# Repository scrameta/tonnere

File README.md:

# Project Tonnere

The EclaireXL was a partially open Atari XL FPGA implementation designed almost
a decade ago. This project is intended to be a fully open community follow-up
version. (It is being renamed **MegaXE**; *tonnere* — deliberately misspelt, to
match "EclaireXL" — is French for thunder, following on from the EclaireXL's
lightning.)

## The Atari core

The FPGA Atari core itself is **not** duplicated here. It lives in the shared
[**atari_xl_fpga_common**](https://github.com/scrameta/atari_xl_fpga_common)
repository — the same core used by the multi-board
[atari_xl_fpga](https://github.com/scrameta/atari_xl_fpga) project — and is
included in this repo as a git submodule at `atari_800xl/common`. This board
project provides the hardware design plus the board-specific top level, clocking,
pin mapping and I/O wrapped around that common core.

## Getting the code

The shared core is a submodule, so clone recursively:

```sh
git clone --recursive https://github.com/scrameta/tonnere

# …or, if you already cloned without --recursive:
git submodule update --init --recursive
```

The core then appears under `atari_800xl/common`. To move onto a newer core
revision, bump the submodule pointer:

```sh
cd atari_800xl/common
git checkout <desired-commit-or-branch>
cd -
git add atari_800xl/common
git commit -m "Bump common core to <rev>"
```

See the
[common repo](https://github.com/scrameta/atari_xl_fpga_common#using-this-repository)
for more on the submodule workflow.

## Status

For now there is only a hardware design, from which a physical board has been
produced. The design goals of this are described below.

## Memory

3 independent banks of RAM from FPGA

- 512KB 16-bit wide 10ns SRAM (for VBXE)
- 2048KB 16-bit wide 10ns SRAM (primary Atari core)
- 32MB 16-bit wide SDRAM (secondary Atari core etc - for large memory expansions, cartridge emulation etc)

## Video output

- HDMI driven directly by FPGA
- Analog video driven by FPGA (3 pins/channel - ~8-bit/channel resolution) filtered/buffered by THS7316.
- NTSC in 480i or 480p, PAL in 576i or 576p
- Polyphasic and area-based scaler allowing 720p, 1080i etc

## Audio output

- PCM5102A DAC

## Audio input

- 12-bit ADC for PBI, SIO, 3.5mm left/right on STM microcontroller

## Joystick ports 1-4

- Directly connected to FPGA (via level shifters)
- Paddle support using STM ADC inputs

## Six USB ports

- 1 USB A internal for keyboard
- 3 USB A external for joystick, keyboard etc
- 1 USB C for power only (next to power switch)
- 1 rear USB C for STM32 DFU (to program it), or to be a mass-storage slave to a PC to copy data on.

## Atari peripheral emulator (ESP32 microcontroller/almost Fujinet)

- Wifi support
- Serial connection to STM32
- SPI master to FPGA (for DMA to RAM, faster than serial via STM)
- SIO pins (all)
- Audio out DAC goes to SIO audio in
- Slave to STM32
- Slave to Atari via SIO
- JTAG for debugging

## Firmware/control (STM32)

- SPI master to FPGA SPI flash chip (to program)
- Can restart FPGA
- SRAM port connected to FPGA (for DMA to Atari core RAM + RAM banks)
- IRQ from FPGA
- 4-bit external SD card interface
- SPI to internal micro SD card (will appear as IDE hard drive to Atari core)
- ADC for sampling (see audio in)
- Serial connection for communication for Atari peripheral emulator
- USB port + stack
- DFU mode for programming, can then program FPGA flash and ESP32 via serial (+BOOT etc).
- HDMI i2c link (to get mode support)
- PLL i2c link (6 programmable clocks for FPGA)
- SWD port for debugging
- UART port for debugging/expansion
- Will run menus etc, via DMA to Atari core (+ potentially framebuffer)

## Atari core (Cyclone 10 LP FPGA)

- Core Atari XL and Atari 800 support
- 2x/4x colour clock Antic/GTIA support
- VBXE
- PokeyMAX
- HDD via IDE emulation on microsd
- Turbo freezer
- Common cartridge banking logic (on RAM)

## Atari ports

- Left cartridge
- PBI with standard extensions (enabled/selected via jumper), 50 pin edge and 50 pin header option.
- SIO (with motor control, without 12V)
- Start/select/option/reset switch headers
- 4 joystick ports

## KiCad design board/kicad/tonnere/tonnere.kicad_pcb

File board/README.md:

# Board status
## 0.51

| Component         | Status | Comment |
| ---               | ---    | --- |
| Audio DAC         |  🟢    | Played a multi-frequency sine wave fine |
| ESP32             |  🟢    | Ran simple pin toggler, also checked it appears on JTAG | 
| ESP32 audio DAC   | ⚪     | |
| ESP32 WIFI        |  🟢    | Fujinet is working fine |
| FPGA              |  🟢    | Working fine. Caution: Do not use clock input pins as outputs!  | 
| FPGA FLASH        |  🟢    | Working fine. Only tested one IC.  | 
| HDMI port         |  🟢    | Tested DVI video output  | 
| JOYSTICK DIR      |  🟢    | Tested toggling pins |
| JOYSTICK PADDLES  | ⚪     |  |
| PLL1              |  🟢    | Programmed via I2C and checked they produce clocks |
| PLL2              |  🟢    | Programmed via I2C and checked they produce clocks |
| SDCARD(EXT)       |  🟢    | Detect insertion/removal. Lists directory on insertion. 4-bit mode. |
| SDCARD(INT)       |  🟢    | Lists directory on boot. spi mode. |
| SDRAM             |  🟢    | Boots to ready | 
| SRAM1             |  🟡    | Used input pins on FPGA, had to correct with a few wires  | 
| SRAM2             |  🟡    | Used input pins on FPGA, had to correct with a few wires  | 
| STM32 ADC         | ⚪     |  | 
| STM32 CORE        |  🟢    | Code running fine. SWD works. USART debug works. | 
| STM32 DFU         |  🟡    | DFU slow to start due to PB5 connected to FPGA flash chip during boot  | 
| STM32 RTC         |  🟢    | Cold starts without battery, keeps time running with battery | 
| STM32 FSMC        |  🟢    | Full bridge to control registers and DMA port implemented | 
| PBI               |  🟢    | Ran turbo freezer ok | 
| SIO               |  🟡    | Motor control did not go via level shifter. Modified that and wired up, now boots | 
| USB               |  🟢    | Tested keyboard in all ports. STM needed patches hub (class + reconnect fix) |
| Video DAC         |  🟡    | Single pin was too aggressive for sigma delta (very low oversampling). Too noisy. Added 2nd pin and used fixed patterns. Achieved 6-bit |

## 0.60

Not made yet...

## Key
| Symbol | Status |
| ---    | ---    |
| ⚪     | Not checked yet |
| 🔴     | Failed |
| 🟡     | Works with workaround |
| 🟢     | Passed |

Passed does not mean thoroughly checked...

<!--
| Feature A | ⚪ | Not checked yet |
| Feature C | 🟡 | Works with workaround |
| Feature D | 🟢 | Passed |
-->

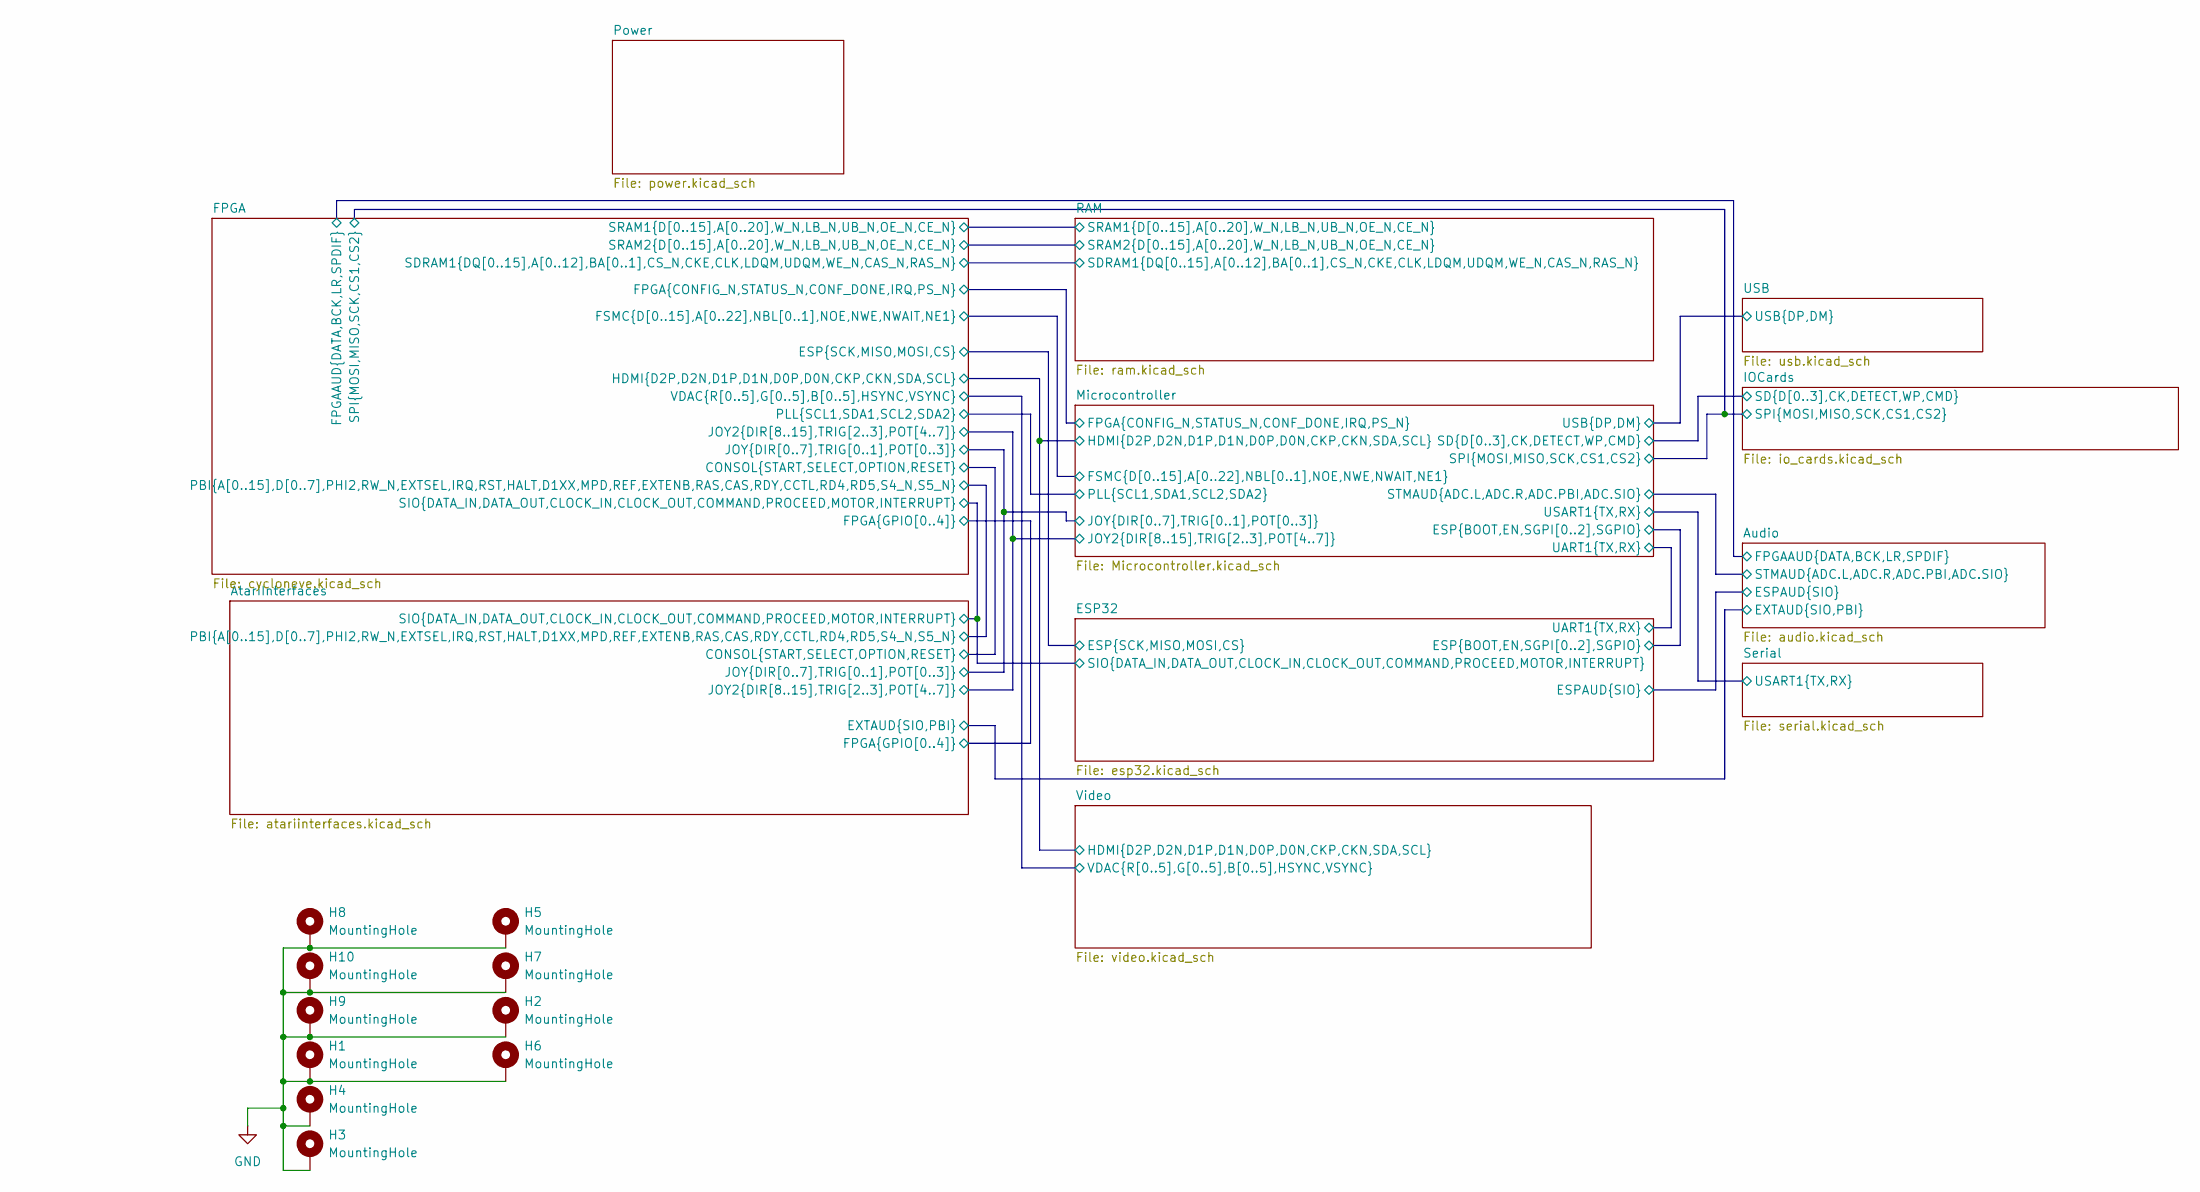
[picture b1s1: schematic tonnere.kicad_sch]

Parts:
H1, H2, H3, H4, H5, H6, H7, H8, H9, H10: MountingHole; MountingHole_4.5mm_Pad_TopBottom

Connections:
GND: H1.1 (1_1), H2.1 (1_1), H3.1 (1_1), H4.1 (1_1), H5.1 (1_1), H6.1 (1_1), H7.1 (1_1), H8.1 (1_1), H9.1 (1_1), H10.1 (1_1); also elsewhere on the board

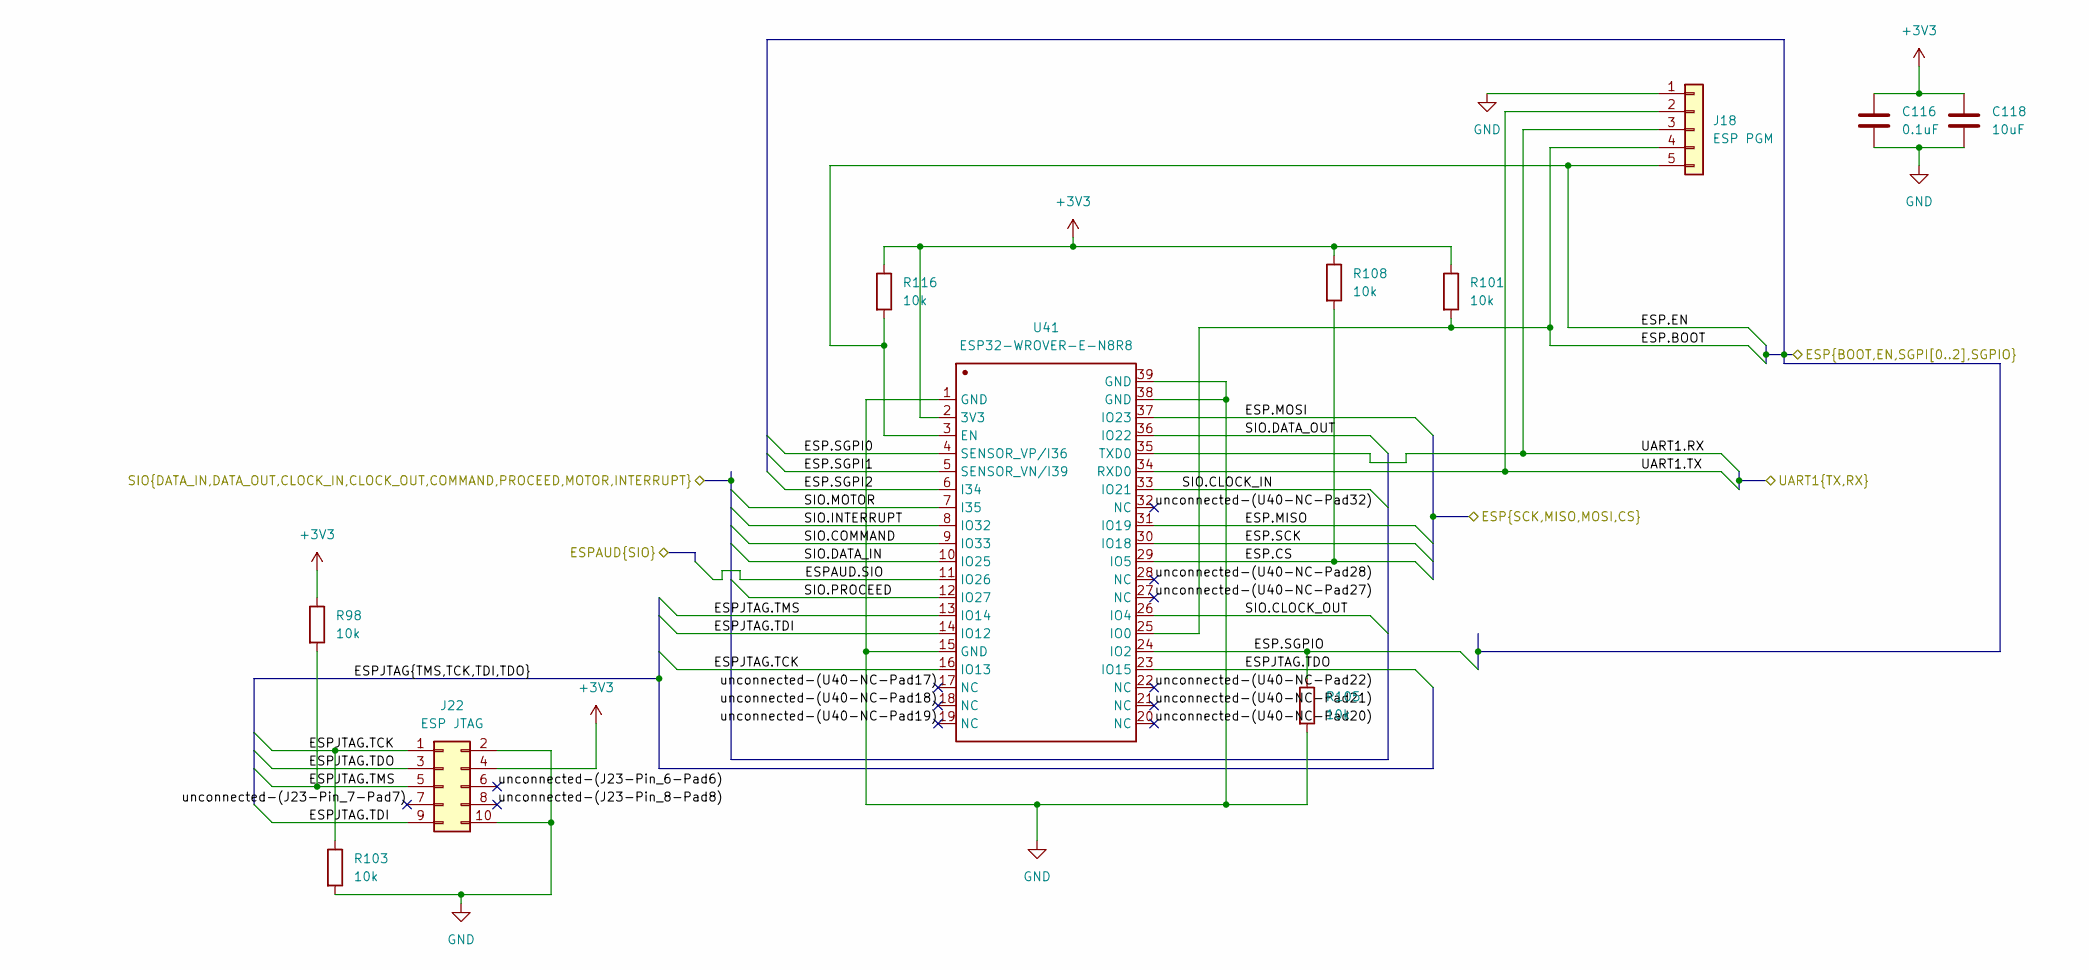
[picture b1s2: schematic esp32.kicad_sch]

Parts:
C116: 0.1uF; C_0603_1608Metric; LCSC C14663
C118: 10uF; C_0805_2012Metric; LCSC C15850
J18: ESP PGM; PinHeader_1x05_P2.54mm_Vertical; LCSC C225480
J22: ESP JTAG; IDC-Header_2x05_P2.54mm_Vertical; LCSC C5665
R98, R101, R103, R105, R108, R116: 10k; R_0603_1608Metric; LCSC C25804
U41: ESP32-WROVER-E-N8R8; WIFI-SMD_ESP32-WROVER-IE8MB; Manufacturer Part ESP32-WROVER-E-N8R8; JLC_3DModel c8095a55cf5447de9fd4c191eac67954

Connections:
+3V3: C116.1, C118.1, J22.4, R98.1, R101.1, R108.1, R116.1, U41.2 (3V3); also elsewhere on the board
/AtariInterfaces/SIO.CLOCK_IN: U41.33 (IO21); also elsewhere on the board
/AtariInterfaces/SIO.CLOCK_OUT: U41.26 (IO4); also elsewhere on the board
/AtariInterfaces/SIO.COMMAND: U41.9 (IO33); also elsewhere on the board
/AtariInterfaces/SIO.DATA_IN: U41.10 (IO25); also elsewhere on the board
/AtariInterfaces/SIO.DATA_OUT: U41.36 (IO22); also elsewhere on the board
/AtariInterfaces/SIO.INTERRUPT: U41.8 (IO32); also elsewhere on the board
/AtariInterfaces/SIO.MOTOR: U41.7 (I35); also elsewhere on the board
/AtariInterfaces/SIO.PROCEED: U41.12 (IO27); also elsewhere on the board
/Audio/ESPAUD.SIO: U41.11 (IO26); also elsewhere on the board
/ESP32/ESP.BOOT: J18.4, R101.2, U41.25 (IO0); also elsewhere on the board
/ESP32/ESP.CS: R108.2, U41.29 (IO5); also elsewhere on the board
/ESP32/ESP.EN: J18.5, R116.2, U41.3 (EN); also elsewhere on the board
/ESP32/ESP.MISO: U41.31 (IO19); also elsewhere on the board
/ESP32/ESP.MOSI: U41.37 (IO23); also elsewhere on the board
/ESP32/ESP.SCK: U41.30 (IO18); also elsewhere on the board
/ESP32/ESP.SGPI0: U41.4 (SENSOR_VP/I36); also elsewhere on the board
/ESP32/ESP.SGPI1: U41.5 (SENSOR_VN/I39); also elsewhere on the board
/ESP32/ESP.SGPI2: U41.6 (I34); also elsewhere on the board
/ESP32/ESP.SGPIO: R105.1, U41.24 (IO2); also elsewhere on the board
/ESP32/ESPJTAG.TCK: J22.1, R103.1, U41.16 (IO13)
/ESP32/ESPJTAG.TDI: J22.9, U41.14 (IO12)
/ESP32/ESPJTAG.TDO: J22.3, U41.23 (IO15)
/ESP32/ESPJTAG.TMS: J22.5, R98.2, U41.13 (IO14)
/ESP32/UART1.RX: J18.3, U41.35 (TXD0); also elsewhere on the board
/ESP32/UART1.TX: J18.2, U41.34 (RXD0); also elsewhere on the board
/ESP32/unconnected-(J23-Pin_6-Pad6): J22.6
/ESP32/unconnected-(J23-Pin_7-Pad7): J22.7
/ESP32/unconnected-(J23-Pin_8-Pad8): J22.8
/ESP32/unconnected-(U40-NC-Pad17): U41.17 (NC)
/ESP32/unconnected-(U40-NC-Pad18): U41.18 (NC)
/ESP32/unconnected-(U40-NC-Pad19): U41.19 (NC)
/ESP32/unconnected-(U40-NC-Pad20): U41.20 (NC)
/ESP32/unconnected-(U40-NC-Pad21): U41.21 (NC)
/ESP32/unconnected-(U40-NC-Pad22): U41.22 (NC)
/ESP32/unconnected-(U40-NC-Pad27): U41.27 (NC)
/ESP32/unconnected-(U40-NC-Pad28): U41.28 (NC)
/ESP32/unconnected-(U40-NC-Pad32): U41.32 (NC)
GND: C116.2, C118.2, J18.1, J22.2, J22.10, R103.2, R105.2, U41.1 (GND), U41.15 (GND), U41.38 (GND), U41.39 (GND); also elsewhere on the board

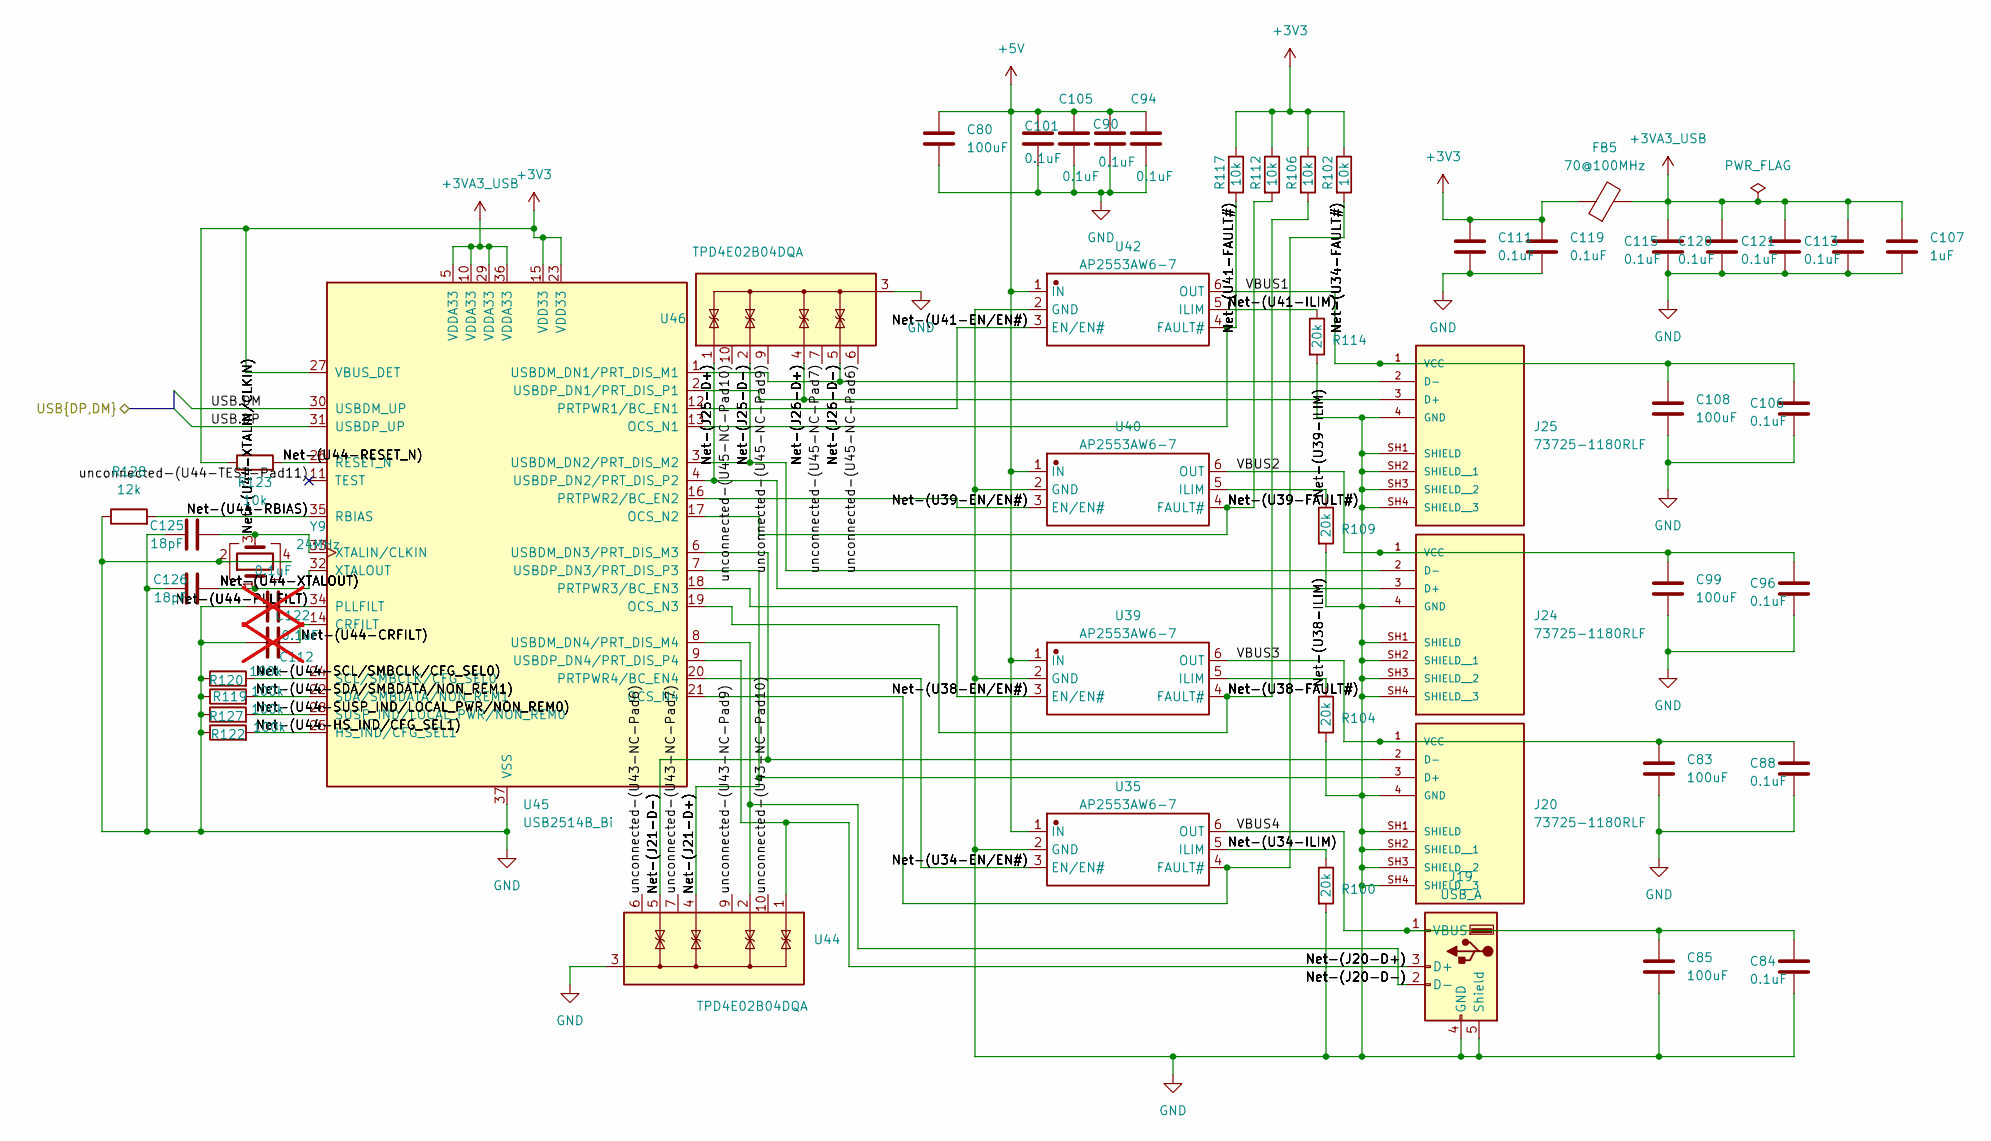
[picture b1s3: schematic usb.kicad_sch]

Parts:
C80, C83, C85, C99, C108: 100uF; C_1206_3216Metric; LCSC C883598
C84, C88, C90, C94, C96, C101, C105, C106, C111, C113, C115, C119, C120, C121: 0.1uF; C_0603_1608Metric; LCSC C14663
C107: 1uF; C_0805_2012Metric; LCSC C28323
C112, C122: 0.1uF; C_0603_1608Metric; LCSC C14663; not fitted
C125, C126: 18pF; C_0603_1608Metric; LCSC C1647
FB5: 70@100MHz; L_0805_2012Metric; LCSC C1012
J19: USB_A; USB_A_Molex_105057_Vertical; LCSC C586225
J20, J24, J25: 73725-1180RLF; AMPHENOL_73725-1180RLF; PARTREV AL1; LCSC C26235
R100, R104, R109, R114: 20k; R_0603_1608Metric; LCSC C4184
R102, R106, R112, R117, R123: 10k; R_0603_1608Metric; LCSC C25804
R119, R120, R122, R127: 100k; R_0603_1608Metric; LCSC C25803
R128: 12k; R_0603_1608Metric; LCSC C22790
U35, U39, U40, U42: AP2553AW6-7; SOT-26_L3.0-W1.6-P0.95-LS2.8-BL; Manufacturer Part AP2553AW6-7; JLC_3DModel df0aaac1b0f04609b13717eddf3d6f89
U44, U46: TPD4E02B04DQA; USON-10_2.5x1.0mm_P0.5mm; LCSC C106794
U45: USB2514B_Bi; QFN-36-1EP_6x6mm_P0.5mm_EP3.7x3.7mm; LCSC C16251
Y9: 24MHz; Crystal_SMD_3225-4Pin_3.2x2.5mm; LCSC C5122304

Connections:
+3V3: C111.1, C119.1, FB5.1, R102.1, R106.1, R112.1, R117.1, R123.1, U45.15 (VDD33), U45.23 (VDD33), U45.27 (VBUS_DET); also elsewhere on the board
+3VA3_USB: C107.1, C113.1, C115.1, C120.1, C121.1, FB5.2, U45.5 (VDDA33), U45.10 (VDDA33), U45.29 (VDDA33), U45.36 (VDDA33)
+5V: C80.1, C90.1, C94.1, C101.1, C105.1, U35.1 (IN), U39.1 (IN), U40.1 (IN), U42.1 (IN); also elsewhere on the board
/Microcontroller/USB.DM: U45.30 (USBDM_UP); also elsewhere on the board
/Microcontroller/USB.DP: U45.31 (USBDP_UP); also elsewhere on the board
/USB/Net-(J20-D+): J19.3 (D+), U44.1 (IO1), U45.9 (USBDP_DN4/PRT_DIS_P4)
/USB/Net-(J20-D-): J19.2 (D-), U44.2 (IO2), U45.8 (USBDM_DN4/PRT_DIS_M4)
/USB/Net-(J21-D+): J20.3 (D+), U44.4 (IO3), U45.7 (USBDP_DN3/PRT_DIS_P3)
/USB/Net-(J21-D-): J20.2 (D-), U44.5 (IO4), U45.6 (USBDM_DN3/PRT_DIS_M3)
/USB/Net-(J25-D+): J24.3 (D+), U45.4 (USBDP_DN2/PRT_DIS_P2), U46.1 (IO1)
/USB/Net-(J25-D-): J24.2 (D-), U45.3 (USBDM_DN2/PRT_DIS_M2), U46.2 (IO2)
/USB/Net-(J26-D+): J25.3 (D+), U45.2 (USBDP_DN1/PRT_DIS_P1), U46.4 (IO3)
/USB/Net-(J26-D-): J25.2 (D-), U45.1 (USBDM_DN1/PRT_DIS_M1), U46.5 (IO4)
/USB/Net-(U34-EN/EN#): U35.3 (EN/EN#), U45.20 (PRTPWR4/BC_EN4)
/USB/Net-(U34-FAULT#): R102.2, U35.4 (FAULT#), U45.21 (OCS_N4)
/USB/Net-(U34-ILIM): R100.1, U35.5 (ILIM)
/USB/Net-(U38-EN/EN#): U39.3 (EN/EN#), U45.18 (PRTPWR3/BC_EN3)
/USB/Net-(U38-FAULT#): R106.2, U39.4 (FAULT#), U45.19 (OCS_N3)
/USB/Net-(U38-ILIM): R104.1, U39.5 (ILIM)
/USB/Net-(U39-EN/EN#): U40.3 (EN/EN#), U45.16 (PRTPWR2/BC_EN2)
/USB/Net-(U39-FAULT#): R112.2, U40.4 (FAULT#), U45.17 (OCS_N2)
/USB/Net-(U39-ILIM): R109.1, U40.5 (ILIM)
/USB/Net-(U41-EN/EN#): U42.3 (EN/EN#), U45.12 (PRTPWR1/BC_EN1)
/USB/Net-(U41-FAULT#): R117.2, U42.4 (FAULT#), U45.13 (OCS_N1)
/USB/Net-(U41-ILIM): R114.1, U42.5 (ILIM)
/USB/Net-(U44-CRFILT): C112.2, U45.14 (CRFILT)
/USB/Net-(U44-HS_IND/CFG_SEL1): R122.2, U45.25 (HS_IND/CFG_SEL1)
/USB/Net-(U44-PLLFILT): C122.2, U45.34 (PLLFILT)
/USB/Net-(U44-RBIAS): R128.2, U45.35 (RBIAS)
/USB/Net-(U44-RESET_N): R123.2, U45.26 (RESET_N)
/USB/Net-(U44-SCL/SMBCLK/CFG_SEL0): R120.2, U45.24 (SCL/SMBCLK/CFG_SEL0)
/USB/Net-(U44-SDA/SMBDATA/NON_REM1): R119.2, U45.22 (SDA/SMBDATA/NON_REM1)
/USB/Net-(U44-SUSP_IND/LOCAL_PWR/NON_REM0): R127.2, U45.28 (SUSP_IND/LOCAL_PWR/NON_REM0)
/USB/Net-(U44-XTALIN/CLKIN): C125.2, U45.33 (XTALIN/CLKIN), Y9.3
/USB/Net-(U44-XTALOUT): C126.2, U45.32 (XTALOUT), Y9.1
/USB/VBUS1: C106.1, C108.1, J25.1 (VCC), U42.6 (OUT)
/USB/VBUS2: C96.1, C99.1, J24.1 (VCC), U40.6 (OUT)
/USB/VBUS3: C83.1, C88.1, J20.1 (VCC), U39.6 (OUT)
/USB/VBUS4: C84.1, C85.1, J19.1 (VBUS), U35.6 (OUT)
/USB/unconnected-(U43-NC-Pad6): U44.6 (NC)
/USB/unconnected-(U43-NC-Pad7): U44.7 (NC)
/USB/unconnected-(U43-NC-Pad9): U44.9 (NC)
/USB/unconnected-(U43-NC-Pad10): U44.10 (NC)
/USB/unconnected-(U44-TEST-Pad11): U45.11 (TEST)
/USB/unconnected-(U45-NC-Pad6): U46.6 (NC)
/USB/unconnected-(U45-NC-Pad7): U46.7 (NC)
/USB/unconnected-(U45-NC-Pad9): U46.9 (NC)
/USB/unconnected-(U45-NC-Pad10): U46.10 (NC)
GND: C80.2, C83.2, C84.2, C85.2, C88.2, C90.2, C94.2, C96.2, C99.2, C101.2, C105.2, C106.2, C107.2, C108.2, C111.2, C112.1, C113.2, C115.2, C119.2, C120.2, C121.2, C122.1, C125.1, C126.1, J19.4 (GND), J19.5 (Shield), J20.4 (GND), J20.SH1 (SHIELD), J20.SH2 (SHIELD__1), J20.SH3 (SHIELD__2), J20.SH4 (SHIELD__3), J24.4 (GND), J24.SH1 (SHIELD), J24.SH2 (SHIELD__1), J24.SH3 (SHIELD__2), J24.SH4 (SHIELD__3), J25.4 (GND), J25.SH1 (SHIELD), J25.SH2 (SHIELD__1), J25.SH3 (SHIELD__2), J25.SH4 (SHIELD__3), R100.2, R104.2, R109.2, R114.2, R119.1, R120.1, R122.1, R127.1, R128.1, U35.2 (GND), U39.2 (GND), U40.2 (GND), U42.2 (GND), U44.3 (G), U44.8 (G), U45.37 (VSS), U46.3 (G), U46.8 (G), Y9.2, Y9.4; also elsewhere on the board

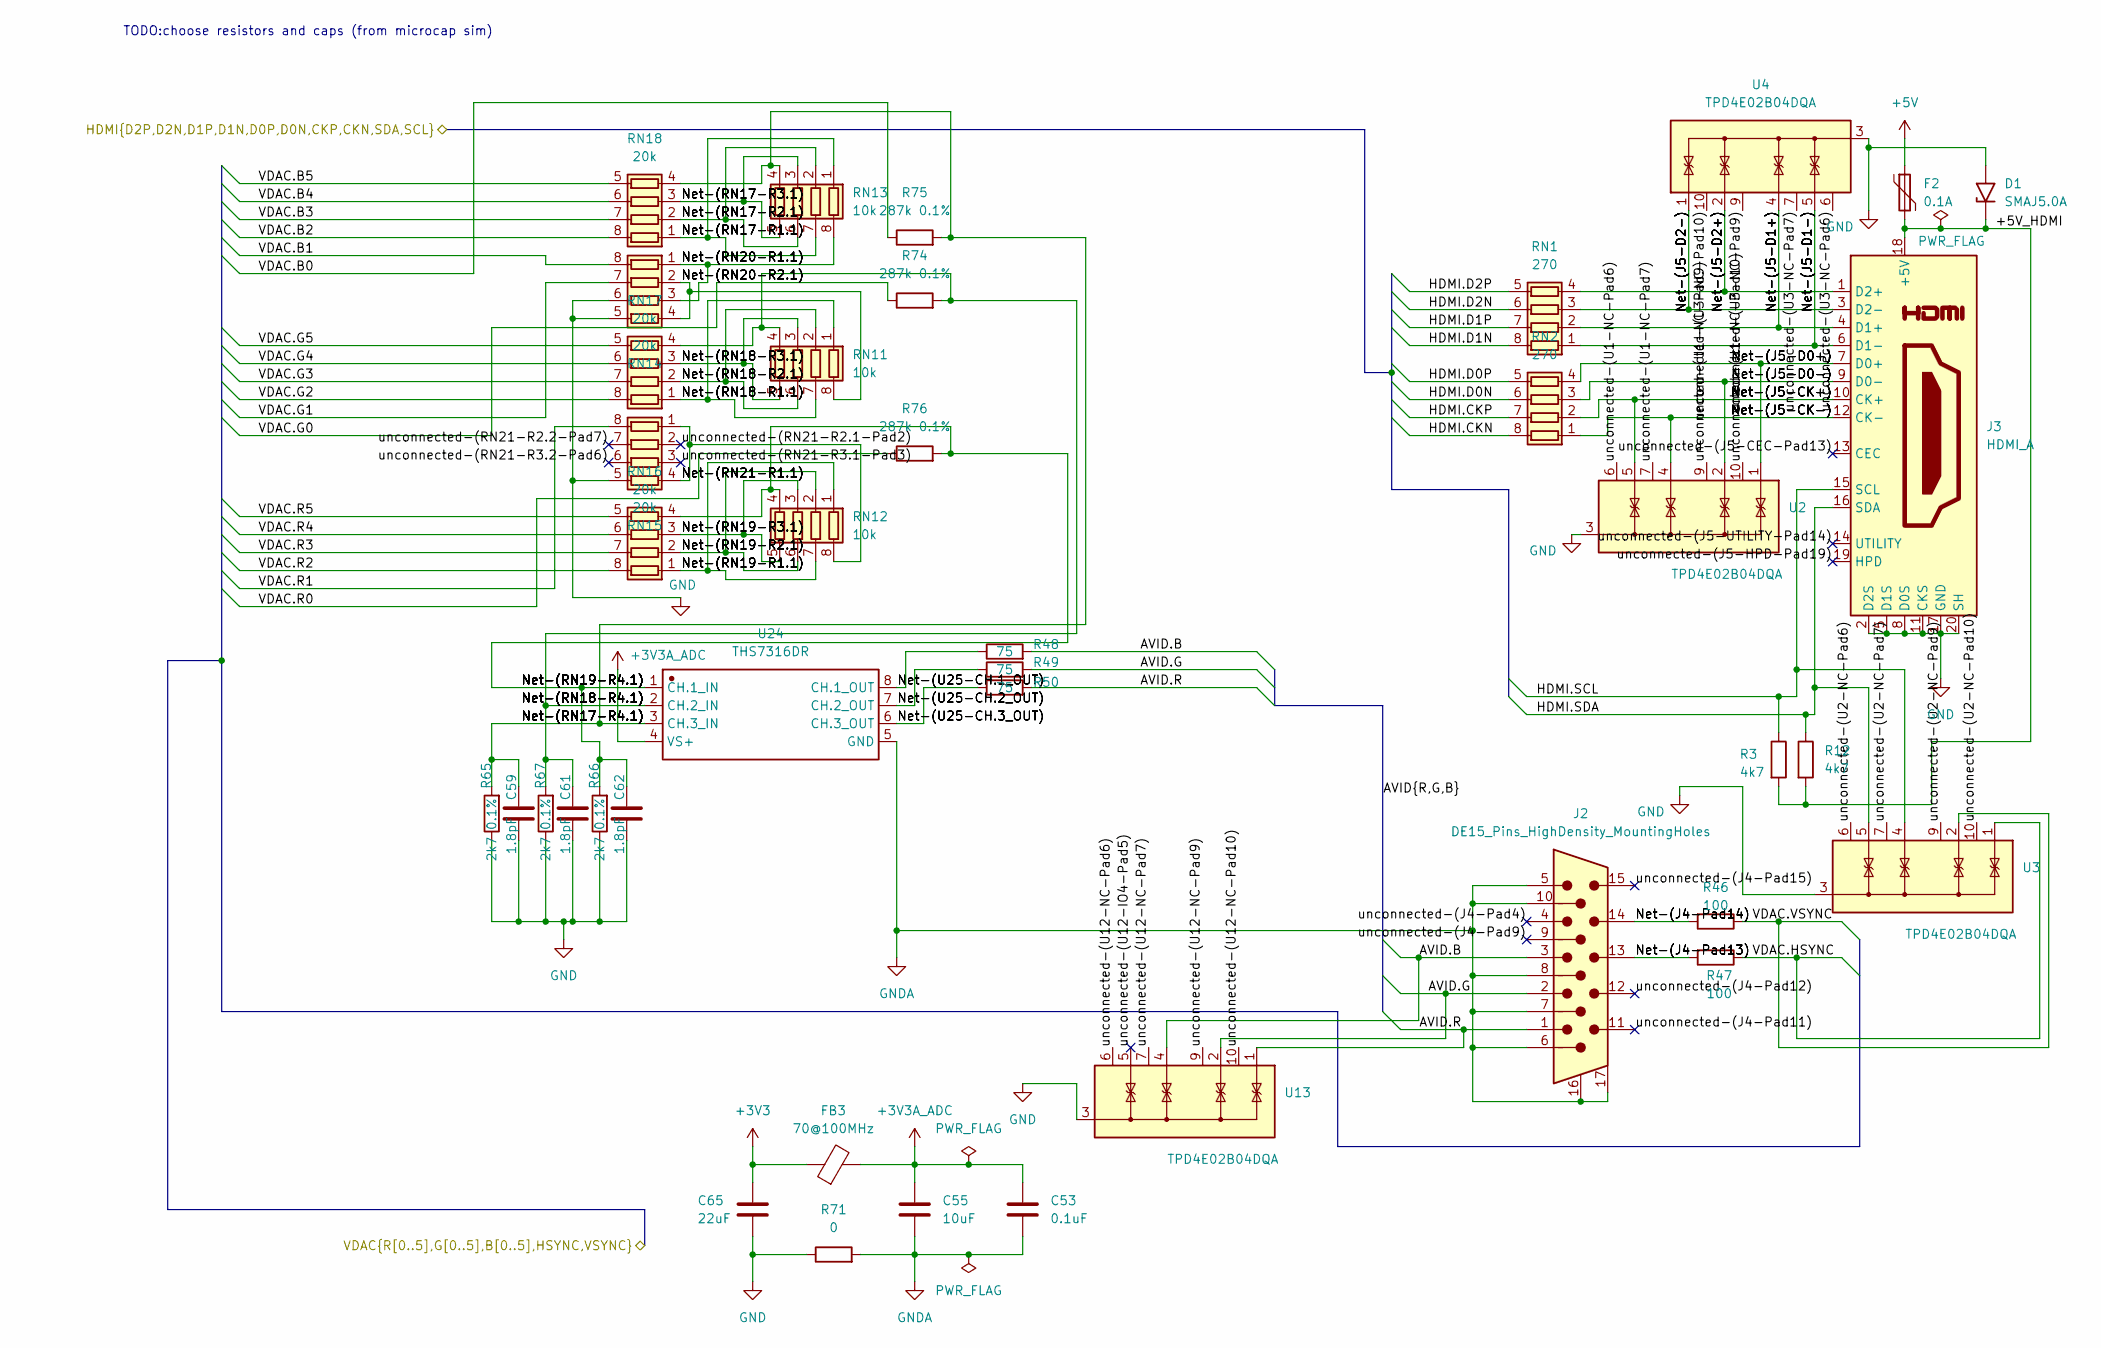
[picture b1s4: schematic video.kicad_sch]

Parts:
C53: 0.1uF; C_0603_1608Metric; LCSC C14663
C55: 10uF; C_0805_2012Metric; LCSC C15850
C59, C61, C62: 1.8pF; C_0603_1608Metric; LCSC C318660
C65: 22uF; C_0805_2012Metric; LCSC C45783
D1: SMAJ5.0A; D_SMA; LCSC C83329
F2: 0.1A; R_0603_1608Metric; LCSC C3760613
FB3: 70@100MHz; L_0805_2012Metric; LCSC C1012
J2: DE15_Pins_HighDensity_MountingHoles; DB9-TH_XDDB-1518-0932; JLC_3DModel 3aa2d893d3fe4a0a80cdfd9bf1095edb
J3: HDMI_A; HDMI-SMD_19P-P0.50-H-F; JLC_3DModel b13a67d988f844af960721e31def9dcc
R3, R12: 4k7; R_0603_1608Metric; LCSC C23162
R46, R47: 100; R_0603_1608Metric; LCSC C22775
R48, R49, R50: 75; R_0603_1608Metric; LCSC C4275
R65, R66, R67: 2k7 0.1%; R_0603_1608Metric; LCSC C705760
R71: 0; R_0805_2012Metric; LCSC C17477
R74, R75, R76: 287k 0.1%; R_0603_1608Metric; LCSC C1870350
RN1, RN2: 270; R_Array_Convex_4x0603; LCSC C1966
RN11, RN12, RN13: 10k; R_Array_Convex_4x0402; LCSC C136853
RN14, RN15, RN16, RN17, RN18: 20k; R_Array_Convex_4x0402; LCSC C728716
U2, U3, U4, U13: TPD4E02B04DQA; USON-10_2.5x1.0mm_P0.5mm; LCSC C106794
U24: THS7316DR; SOIC-8_L5.0-W4.0-P1.27-LS6.1-BL; Manufacturer Part THS7316DR; JLC_3DModel a504e76c6a8144b285f2253095d55ec7

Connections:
+3V3: C65.1, FB3.1; also elsewhere on the board
+3V3A_ADC: C53.1, C55.1, FB3.2, U24.4 (VS+)
+5V: F2.1; also elsewhere on the board
/FPGA/HDMI.CKN: RN2.8 (R1.2); also elsewhere on the board
/FPGA/HDMI.CKP: RN2.7 (R2.2); also elsewhere on the board
/FPGA/HDMI.D0N: RN2.6 (R3.2); also elsewhere on the board
/FPGA/HDMI.D0P: RN2.5 (R4.2); also elsewhere on the board
/FPGA/HDMI.D1N: RN1.8 (R1.2); also elsewhere on the board
/FPGA/HDMI.D1P: RN1.7 (R2.2); also elsewhere on the board
/FPGA/HDMI.D2N: RN1.6 (R3.2); also elsewhere on the board
/FPGA/HDMI.D2P: RN1.5 (R4.2); also elsewhere on the board
/FPGA/HDMI.SCL: J3.15 (SCL), R3.1, U3.4 (IO3); also elsewhere on the board
/FPGA/HDMI.SDA: J3.16 (SDA), R12.1, U3.5 (IO4); also elsewhere on the board
/FPGA/VDAC.B0: R75.1; also elsewhere on the board
/FPGA/VDAC.B1: RN14.8 (R1.2); also elsewhere on the board
/FPGA/VDAC.B2: RN18.8 (R1.2); also elsewhere on the board
/FPGA/VDAC.B3: RN18.7 (R2.2); also elsewhere on the board
/FPGA/VDAC.B4: RN18.6 (R3.2); also elsewhere on the board
/FPGA/VDAC.B5: RN18.5 (R4.2); also elsewhere on the board
/FPGA/VDAC.G0: R74.1; also elsewhere on the board
/FPGA/VDAC.G1: RN14.7 (R2.2); also elsewhere on the board
/FPGA/VDAC.G2: RN17.8 (R1.2); also elsewhere on the board
/FPGA/VDAC.G3: RN17.7 (R2.2); also elsewhere on the board
/FPGA/VDAC.G4: RN17.6 (R3.2); also elsewhere on the board
/FPGA/VDAC.G5: RN17.5 (R4.2); also elsewhere on the board
/FPGA/VDAC.HSYNC: R47.1, U3.1 (IO1); also elsewhere on the board
/FPGA/VDAC.R0: R76.1; also elsewhere on the board
/FPGA/VDAC.R1: RN15.8 (R1.2); also elsewhere on the board
/FPGA/VDAC.R2: RN16.8 (R1.2); also elsewhere on the board
/FPGA/VDAC.R3: RN16.7 (R2.2); also elsewhere on the board
/FPGA/VDAC.R4: RN16.6 (R3.2); also elsewhere on the board
/FPGA/VDAC.R5: RN16.5 (R4.2); also elsewhere on the board
/FPGA/VDAC.VSYNC: R46.1, U3.2 (IO2); also elsewhere on the board
/Video/+5V_HDMI: D1.1 (A1), F2.2, J3.18 (+5V), R3.2, R12.2
/Video/AVID.B: J2.3, R48.2, U13.4 (IO3)
/Video/AVID.G: J2.2, R49.2, U13.2 (IO2)
/Video/AVID.R: J2.1, R50.2, U13.1 (IO1)
/Video/Net-(J4-Pad13): J2.13, R47.2
/Video/Net-(J4-Pad14): J2.14, R46.2
/Video/Net-(J5-CK+): J3.10 (CK+), RN2.2 (R2.1), U2.5 (IO4)
/Video/Net-(J5-CK-): J3.12 (CK-), RN2.1 (R1.1), U2.4 (IO3)
/Video/Net-(J5-D0+): J3.7 (D0+), RN2.4 (R4.1), U2.1 (IO1)
/Video/Net-(J5-D0-): J3.9 (D0-), RN2.3 (R3.1), U2.2 (IO2)
/Video/Net-(J5-D1+): J3.4 (D1+), RN1.2 (R2.1), U4.4 (IO3)
/Video/Net-(J5-D1-): J3.6 (D1-), RN1.1 (R1.1), U4.5 (IO4)
/Video/Net-(J5-D2+): J3.1 (D2+), RN1.4 (R4.1), U4.2 (IO2)
/Video/Net-(J5-D2-): J3.3 (D2-), RN1.3 (R3.1), U4.1 (IO1)
/Video/Net-(RN17-R1.1): RN13.1 (R1.1), RN13.7 (R2.2), RN18.1 (R1.1)
/Video/Net-(RN17-R2.1): RN13.2 (R2.1), RN13.6 (R3.2), RN18.2 (R2.1)
/Video/Net-(RN17-R3.1): RN13.3 (R3.1), RN13.5 (R4.2), RN18.3 (R3.1)
/Video/Net-(RN17-R4.1): C59.1, R65.2, R75.2, RN13.4 (R4.1), RN18.4 (R4.1), U24.3 (CH.3_IN)
/Video/Net-(RN18-R1.1): RN11.1 (R1.1), RN11.7 (R2.2), RN17.1 (R1.1)
/Video/Net-(RN18-R2.1): RN11.2 (R2.1), RN11.6 (R3.2), RN17.2 (R2.1)
/Video/Net-(RN18-R3.1): RN11.3 (R3.1), RN11.5 (R4.2), RN17.3 (R3.1)
/Video/Net-(RN18-R4.1): C61.1, R67.2, R74.2, RN11.4 (R4.1), RN17.4 (R4.1), U24.2 (CH.2_IN)
/Video/Net-(RN19-R1.1): RN12.1 (R1.1), RN12.7 (R2.2), RN16.1 (R1.1)
/Video/Net-(RN19-R2.1): RN12.2 (R2.1), RN12.6 (R3.2), RN16.2 (R2.1)
/Video/Net-(RN19-R3.1): RN12.3 (R3.1), RN12.5 (R4.2), RN16.3 (R3.1)
/Video/Net-(RN19-R4.1): C62.1, R66.2, R76.2, RN12.4 (R4.1), RN16.4 (R4.1), U24.1 (CH.1_IN)
/Video/Net-(RN20-R1.1): RN13.8 (R1.2), RN14.1 (R1.1), RN14.3 (R3.1)
/Video/Net-(RN20-R2.1): RN11.8 (R1.2), RN14.2 (R2.1), RN14.4 (R4.1)
/Video/Net-(RN21-R1.1): RN12.8 (R1.2), RN15.1 (R1.1), RN15.4 (R4.1)
/Video/Net-(U25-CH.1_OUT): R48.1, U24.8 (CH.1_OUT)
/Video/Net-(U25-CH.2_OUT): R49.1, U24.7 (CH.2_OUT)
/Video/Net-(U25-CH.3_OUT): R50.1, U24.6 (CH.3_OUT)
/Video/unconnected-(J4-Pad4): J2.4
/Video/unconnected-(J4-Pad9): J2.9
/Video/unconnected-(J4-Pad11): J2.11
/Video/unconnected-(J4-Pad12): J2.12
/Video/unconnected-(J4-Pad15): J2.15
/Video/unconnected-(J5-CEC-Pad13): J3.13 (CEC)
/Video/unconnected-(J5-HPD-Pad19): J3.19 (HPD)
/Video/unconnected-(J5-UTILITY-Pad14): J3.14 (UTILITY)
/Video/unconnected-(RN21-R2.1-Pad2): RN15.2 (R2.1)
/Video/unconnected-(RN21-R2.2-Pad7): RN15.7 (R2.2)
/Video/unconnected-(RN21-R3.1-Pad3): RN15.3 (R3.1)
/Video/unconnected-(RN21-R3.2-Pad6): RN15.6 (R3.2)
/Video/unconnected-(U1-NC-Pad6): U2.6 (NC)
/Video/unconnected-(U1-NC-Pad7): U2.7 (NC)
/Video/unconnected-(U1-NC-Pad9): U2.9 (NC)
/Video/unconnected-(U1-NC-Pad10): U2.10 (NC)
/Video/unconnected-(U2-NC-Pad6): U3.6 (NC)
/Video/unconnected-(U2-NC-Pad7): U3.7 (NC)
/Video/unconnected-(U2-NC-Pad9): U3.9 (NC)
/Video/unconnected-(U2-NC-Pad10): U3.10 (NC)
/Video/unconnected-(U3-NC-Pad6): U4.6 (NC)
/Video/unconnected-(U3-NC-Pad7): U4.7 (NC)
/Video/unconnected-(U3-NC-Pad9): U4.9 (NC)
/Video/unconnected-(U3-NC-Pad10): U4.10 (NC)
/Video/unconnected-(U12-IO4-Pad5): U13.5 (IO4)
/Video/unconnected-(U12-NC-Pad6): U13.6 (NC)
/Video/unconnected-(U12-NC-Pad7): U13.7 (NC)
/Video/unconnected-(U12-NC-Pad9): U13.9 (NC)
/Video/unconnected-(U12-NC-Pad10): U13.10 (NC)
GND: C59.2, C61.2, C62.2, C65.2, D1.2 (A2), J3.2 (D2S), J3.5 (D1S), J3.8 (D0S), J3.11 (CKS), J3.17 (GND), J3.20 (SH), J3.21 (SH), J3.22 (SH), J3.23 (SH), R65.1, R66.1, R67.1, R71.1, RN14.5 (R4.2), RN14.6 (R3.2), RN15.5 (R4.2), U2.3 (G), U2.8 (G), U3.3 (G), U3.8 (G), U4.3 (G), U4.8 (G), U13.3 (G), U13.8 (G); also elsewhere on the board
GNDA: C53.2, C55.2, J2.5, J2.6, J2.7, J2.8, J2.10, J2.16, J2.17, R71.2, U24.5 (GND); also elsewhere on the board

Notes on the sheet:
TODO:choose resistors and caps (from microcap sim)

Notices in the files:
keyboard/Badge/BadgeLights/BadgeLights.kicad_pcb:
TinyLights rev. 1 (c) 2026 Bertrand Le Roy - https://github.com/bleroy/3d-junkyard
keyboard/MegaXE-keyboard.kicad_pcb:
© Bertrand Le Roy 2026
